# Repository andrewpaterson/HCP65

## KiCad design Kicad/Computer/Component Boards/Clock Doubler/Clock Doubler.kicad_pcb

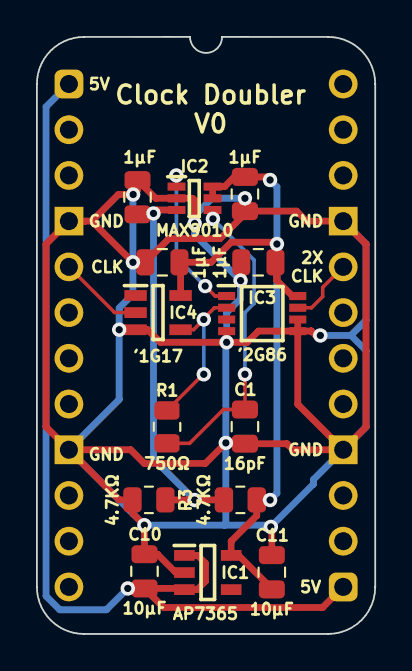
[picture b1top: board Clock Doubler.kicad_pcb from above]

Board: 2 copper layers, 18.8 x 33.2 mm, 15 parts (0 on the bottom side), 9 nets.

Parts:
C1: 16pF; C_0805
C2, C3, C4, C5: 1μF; C_0805
C10, C11: 10µF; C_0805
IC1: AP7365-33WG-7; SOT95P285X130-5N
IC2: MAX9010EXT+T; SOT65P210X110-6N
IC3: 74LVC2G86DP,125; SOP65P400X110-8N
IC4: 74LVC1G17GV,125; SOT95P275X110-5N
J1: Board 2x12 W15.24mm; DIP-24_Board_W15.24mm
R1: 750Ω; R_0805
R2, R3: 4.7KΩ; R_0805

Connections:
2x Fast CLK: IC3.7 (1Y), J1.20
5V: C10.1, IC1.1 (6VIn), IC1.3 (EN), J1.1, J1.13
/1.6V: C2.1, IC2.3 (IN+), R2.1, R3.2
/3.3V: C3.1, C4.1, C5.1, C11.1, IC1.5 (3.3VOut), IC2.5 (VCC), IC2.6 (VCC), IC3.8 (VCC), IC4.5 (3V), R2.2
/Clean Fast CLK: IC3.2 (1B), IC4.4 (Y), R1.2
Fast CLK: IC4.2 (A), J1.5
GND: C1.1, C2.2, C3.2, C4.2, C5.2, C10.2, C11.2, IC1.2 (GND), IC2.2 (GND), IC3.4 (GND), IC3.5 (2A), IC3.6 (2B), IC4.3 (GND), J1.4, J1.9, J1.16, J1.21, R3.1
unnamed: C1.2, IC2.4 (IN-), R1.1
unnamed: IC2.1 (OUT), IC3.1 (1A)

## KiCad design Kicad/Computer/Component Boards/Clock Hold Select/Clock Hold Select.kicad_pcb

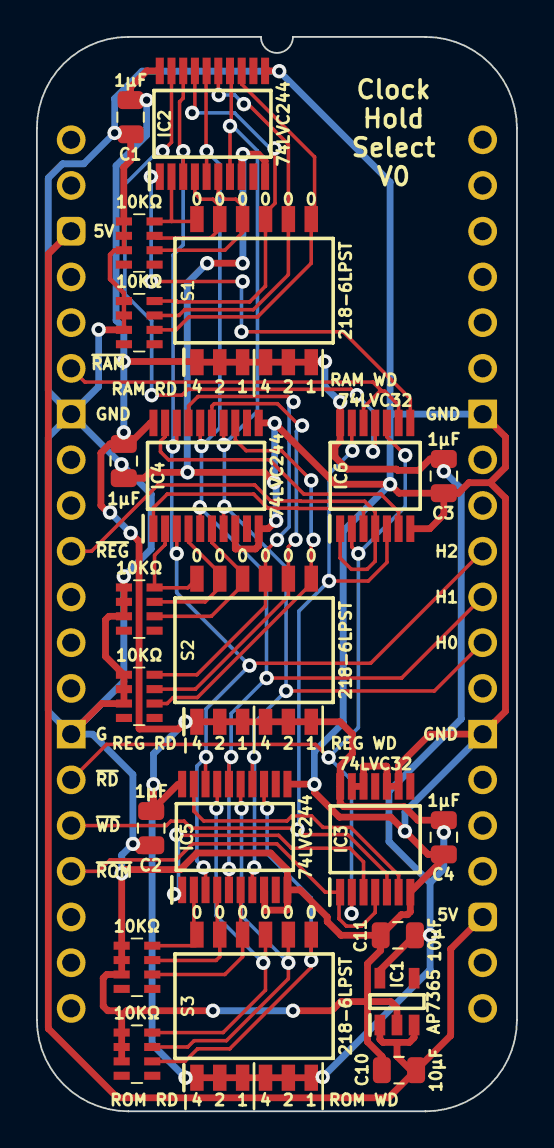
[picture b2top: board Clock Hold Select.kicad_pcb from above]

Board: 2 copper layers, 26.7 x 59.7 mm, 23 parts (0 on the bottom side), 35 nets.

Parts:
C1, C2, C3, C4, C12: 1μF; C_0805
C10, C11: 10µF; C_0805
IC1: AP7365-33WG-7; SOT95P285X130-5N
IC2, IC4, IC5: 74LVC244APW,118; SOP65P640X110-20N
IC3, IC6: 74LVC32APW,118; SOP65P640X110-14N
J1: Board 2x20 W22.86mm; DIP-40_Board_W22.86mm
RN1, RN2, RN3, RN4, RN5, RN6: CAY16-103J4LF; CAY16-J4
S1, S2, S3: 218-6LPST; SOIC127P844X265-12N

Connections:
5V: C10.1, IC1.1 (6VIn), IC1.3 (EN), J1.3, J1.23
/3.3V: C1.1, C2.1, C3.1, C4.1, C11.1, C12.1, IC1.5 (3.3VOut), IC2.20 (3V), IC3.14 (3V), IC4.20 (3V), IC5.20 (3V), IC6.14 (3V), S1.1, S1.2, S1.3, S1.4, S1.5, S1.6, S2.1, S2.2, S2.3, S2.4, S2.5, S2.6, S3.1, S3.2, S3.3, S3.4, S3.5, S3.6
/RAM RD H0: IC2.6 (1A2), RN1.6 (R3), S1.10
/RAM RD H1: IC2.4 (1A1), RN1.7 (R2), S1.11
/RAM RD H2: IC2.2 (1A0), RN1.8 (R1), S1.12
/RAM WD H0: IC2.13 (2A2), RN2.6 (R3), S1.7
/RAM WD H1: IC2.15 (2A1), RN2.7 (R2), S1.8
/RAM WD H2: IC2.17 (2A0), RN2.8 (R1), S1.9
/REG RD H0: IC4.6 (1A2), RN3.6 (R3), S2.10
/REG RD H1: IC4.4 (1A1), RN3.7 (R2), S2.11
/REG RD H2: IC4.2 (1A0), RN3.8 (R1), S2.12
/REG WD H0: IC4.13 (2A2), RN4.6 (R3), S2.7
/REG WD H1: IC4.15 (2A1), RN4.7 (R2), S2.8
/REG WD H2: IC4.17 (2A0), RN4.8 (R1), S2.9
/ROM RD H0: IC5.6 (1A2), RN5.6 (R3), S3.10
/ROM RD H1: IC5.4 (1A1), RN5.7 (R2), S3.11
/ROM RD H2: IC5.2 (1A0), RN5.8 (R1), S3.12
/ROM WD H0: IC5.13 (2A2), RN6.6 (R3), S3.7
/ROM WD H1: IC5.15 (2A1), RN6.7 (R2), S3.8
/ROM WD H2: IC5.17 (2A0), RN6.8 (R1), S3.9
/~RAM+~RD: IC2.1 (~1OE), IC6.8 (3Y)
/~RAM+~WD: IC2.19 (~2OE), IC6.11 (4Y)
/~REG+~RD: IC4.1 (~1OE), IC6.3 (1Y)
/~REG+~WD: IC4.19 (~2OE), IC6.6 (2Y)
/~ROM+~RD: IC3.3 (1Y), IC5.1 (~1OE)
/~ROM+~WD: IC3.6 (2Y), IC5.19 (~2OE)
GND: C1.2, C2.2, C3.2, C4.2, C10.2, C11.2, C12.2, IC1.2 (GND), IC2.8 (1A3), IC2.10 (GND), IC2.11 (2A3), IC3.7 (GND), IC3.9 (3A), IC3.10 (3B), IC3.12 (4A), IC3.13 (4B), IC4.8 (1A3), IC4.10 (GND), IC4.11 (2A3), IC5.8 (1A3), IC5.10 (GND), IC5.11 (2A3), IC6.7 (GND), J1.7, J1.14, J1.27, J1.34, RN1.1 (R1), RN1.2 (R2), RN1.3 (R3), RN2.1 (R1), RN2.2 (R2), RN2.3 (R3), RN3.1 (R1), RN3.2 (R2), RN3.3 (R3), RN4.1 (R1), RN4.2 (R2), RN4.3 (R3), RN5.1 (R1), RN5.2 (R2), RN5.3 (R3), RN6.1 (R1), RN6.2 (R2), RN6.3 (R3)
H0: IC2.7 (2Y2), IC2.14 (1Y2), IC4.7 (2Y2), IC4.14 (1Y2), IC5.7 (2Y2), IC5.14 (1Y2), J1.29
H1: IC2.5 (2Y1), IC2.16 (1Y1), IC4.5 (2Y1), IC4.16 (1Y1), IC5.5 (2Y1), IC5.16 (1Y1), J1.30
H2: IC2.3 (2Y0), IC2.18 (1Y0), IC4.3 (2Y0), IC4.18 (1Y0), IC5.3 (2Y0), IC5.18 (1Y0), J1.31
~Device RAM: IC6.9 (3A), IC6.12 (4A), J1.6
~Device ROM: IC3.1 (1A), IC3.4 (2A), J1.17
~Device Registers: IC6.1 (1A), IC6.4 (2A), J1.10
~RD: IC3.2 (1B), IC6.2 (1B), IC6.10 (3B), J1.15
~WD: IC3.5 (2B), IC6.5 (2B), IC6.13 (4B), J1.16

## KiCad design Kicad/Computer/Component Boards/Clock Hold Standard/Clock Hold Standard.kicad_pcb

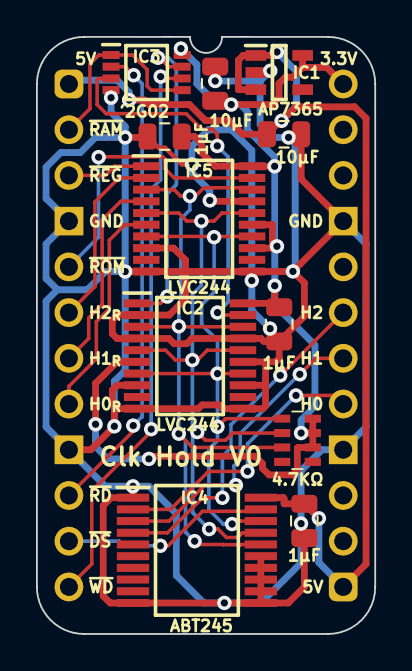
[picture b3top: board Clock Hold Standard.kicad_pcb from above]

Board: 2 copper layers, 18.8 x 33.2 mm, 12 parts (0 on the bottom side), 20 nets.

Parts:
C1, C2, C4: 1μF; C_0805
C10, C11: 10µF; C_0805
IC1: AP7365-33WG-7; SOT95P285X130-5N
IC2, IC5: 74LVC244APW,118; SOP65P640X110-20N
IC3: 74LVC2G02DP,125; SOP65P400X110-8N
IC4: SN74ABT245BDBR; SOP65P780X200-20N
J1: Board 2x12 W15.24mm; DIP-24_Board_W15.24mm
RN1: CAY16-472J4LF; CAY16-F4

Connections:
3.3V: C1.1, C2.1, C11.1, IC1.5 (3.3VOut), IC2.6 (1A2), IC2.20 (3V), IC3.8 (3V), IC5.13 (2A2), IC5.15 (2A1), IC5.20 (3V), J1.24, RN1.6 (R3), RN1.7 (R2), RN1.8 (R1)
5V: C4.1, C10.1, IC1.1 (6VIn), IC1.3 (EN), IC4.20 (5V), J1.1, J1.13
/H0: IC2.7 (2Y2), IC2.14 (1Y2), IC4.18 (B0), IC5.7 (2Y2), IC5.14 (1Y2), RN1.1 (R1)
/H1: IC2.5 (2Y1), IC2.16 (1Y1), IC4.17 (B1), IC5.5 (2Y1), IC5.16 (1Y1), RN1.2 (R2)
/H2: IC2.3 (2Y0), IC2.18 (1Y0), IC4.16 (B2), IC5.3 (2Y0), IC5.18 (1Y0), RN1.3 (R3)
/~RAM+~RD: IC2.1 (~1OE), IC3.7 (1Y)
/~RAM+~WD: IC2.19 (~2OE), IC3.3 (2Y)
GND: C1.2, C2.2, C4.2, C10.2, C11.2, IC1.2 (GND), IC2.2 (1A0), IC2.4 (1A1), IC2.8 (1A3), IC2.10 (GND), IC2.11 (2A3), IC2.13 (2A2), IC2.15 (2A1), IC2.17 (2A0), IC3.4 (GND), IC4.1 (DIR), IC4.10 (GND), IC4.11 (B7), IC4.12 (B6), IC4.13 (B5), IC4.14 (B4), IC4.15 (B3), IC5.8 (1A3), IC5.10 (GND), IC5.11 (2A3), IC5.17 (2A0), J1.4, J1.9, J1.16, J1.21
H0_{OUT}: IC4.2 (A0), J1.17
H0_{REG}: IC5.6 (1A2), J1.8
H1_{OUT}: IC4.3 (A1), J1.18
H1_{REG}: IC5.4 (1A1), J1.7
H2_{OUT}: IC4.4 (A2), J1.19
H2_{REG}: IC5.2 (1A0), J1.6
~Device RAM: IC3.1 (1A), IC3.5 (2A), J1.2
~Device ROM: IC5.19 (~2OE), J1.5
~Device Registers: IC5.1 (~1OE), J1.3
~Device Select: IC4.19 (~OE), J1.11
~RD: IC3.2 (1B), J1.10
~WD: IC3.6 (2B), J1.12

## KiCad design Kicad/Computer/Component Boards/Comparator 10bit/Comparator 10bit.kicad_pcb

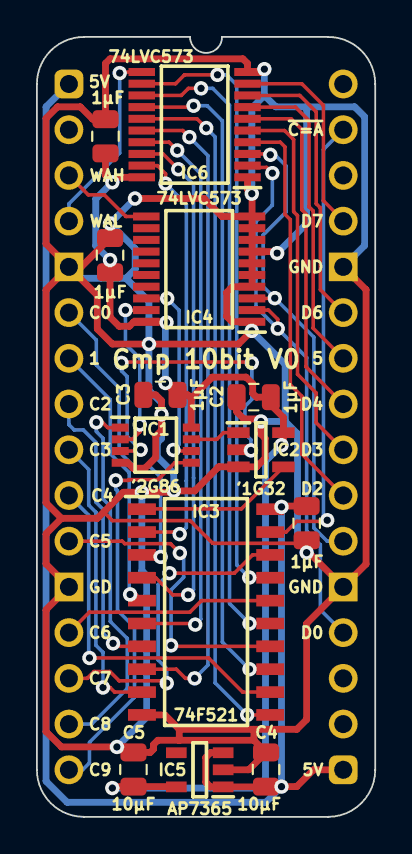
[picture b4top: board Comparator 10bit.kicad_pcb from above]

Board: 2 copper layers, 18.8 x 43.3 mm, 14 parts (0 on the bottom side), 37 nets.

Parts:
C1, C2, C3, C11, C12: 1μF; C_0805
C4, C5: 10µF; C_0805
IC1: 74LVC2G86DP,125; SOP65P400X110-8N
IC2: 74LVC1G32GV,125; SOT95P275X110-5N
IC3: SN74F521NSR; SOIC127P780X200-20N
IC4, IC6: 74LVC573APW,118; SOP65P640X110-20N
IC5: AP7365-33WG-7; SOT95P285X130-5N
J1: Board 2x16 W15.24mm; DIP-32_Board_W15.24mm

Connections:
5V: C4.1, C12.1, IC3.20 (5V), IC5.1 (6VIn), IC5.3 (EN), J1.1, J1.17
/3.3V: C1.1, C2.1, C3.1, C5.1, C11.1, IC1.8 (VCC), IC2.5 (3V), IC4.20 (3V), IC5.5 (3.3VOut), IC6.20 (3V)
/A0: IC3.2 (P0), IC6.19 (Q0)
/A1: IC3.4 (P1), IC6.18 (Q1)
/A2: IC3.6 (P2), IC6.17 (Q2)
/A3: IC3.8 (P3), IC6.16 (Q3)
/A4: IC3.11 (P4), IC6.15 (Q4)
/A5: IC3.13 (P5), IC6.14 (Q5)
/A6: IC3.15 (P6), IC6.13 (Q6)
/A7: IC3.17 (P7), IC6.12 (Q7)
/A8: IC1.2 (1B), IC4.19 (Q0)
/A8⊕C8: IC1.7 (1Y), IC2.1 (B)
/A9: IC1.6 (2B), IC4.18 (Q1)
/A9⊕C9: IC1.3 (2Y), IC2.2 (A)
/~C_{8..9=A_{8..9}}: IC2.4 (Y), IC3.1 (~OE)
C0: IC3.3 (Q0), J1.6
C1: IC3.5 (Q1), J1.7
C2: IC3.7 (Q2), J1.8
C3: IC3.9 (Q3), J1.9
C4: IC3.12 (Q4), J1.10
C5: IC3.14 (Q5), J1.11
C6: IC3.16 (Q6), J1.13
C7: IC3.18 (Q7), J1.14
C8: IC1.1 (1A), J1.15
C9: IC1.5 (2A), J1.16
D0: IC4.2 (D0), IC6.2 (D0), J1.20
D1: IC4.3 (D1), IC6.3 (D1), J1.22
D2: IC6.4 (D2), J1.23
D3: IC6.5 (D3), J1.24
D4: IC6.6 (D4), J1.25
D5: IC6.7 (D5), J1.26
D6: IC6.8 (D6), J1.27
D7: IC6.9 (D7), J1.29
GND: C1.2, C2.2, C3.2, C4.2, C5.2, C11.2, C12.2, IC1.4 (GND), IC2.3 (GND), IC3.10 (GND), IC4.1 (~OE), IC4.4 (D2), IC4.5 (D3), IC4.6 (D4), IC4.7 (D5), IC4.8 (D6), IC4.9 (D7), IC4.10 (GND), IC5.2 (GND), IC6.1 (~OE), IC6.10 (GND), J1.5, J1.12, J1.21, J1.28
Write A High: IC4.11 (LE), J1.3
Write A Low: IC6.11 (LE), J1.4
~C=A: IC3.19 (~P=Q), J1.31

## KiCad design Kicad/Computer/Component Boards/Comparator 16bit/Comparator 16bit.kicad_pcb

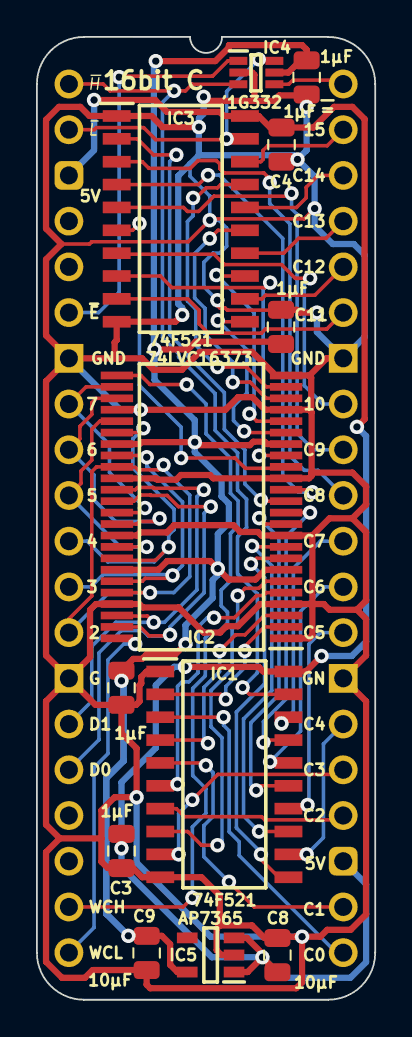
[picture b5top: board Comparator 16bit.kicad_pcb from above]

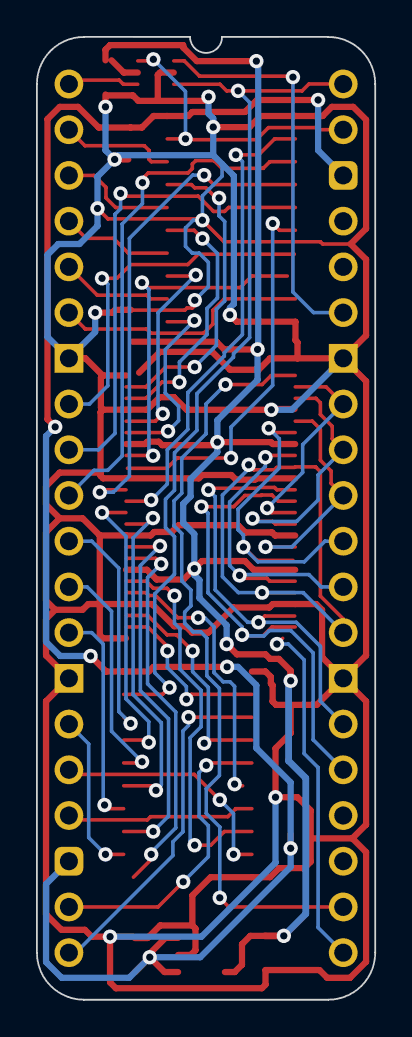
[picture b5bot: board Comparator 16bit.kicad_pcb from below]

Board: 2 copper layers, 18.8 x 53.5 mm, 15 parts (2 on the bottom side), 49 nets.

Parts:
C1, C2, C3, C4, C5: 1μF; C_0805
C8, C9: 10µF; C_0805
IC1, IC3: SN74F521NSR; SOIC127P780X200-20N
IC2: 74LVC16373ADL,118; SOP64P1025X280-48N
IC4: SN74LVC1G332DCKR; SOT65P210X110-6N
IC5: AP7365-33WG-7; SOT95P285X130-5N
J1, J3: Pin_Header_01x20; PinHeader_1x20_P2.54mm_Vertical
J2: Board 2x20 W15.24mm; DIP-40_Board_W15.24mm

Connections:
5V: C3.1, C4.1, C8.1, IC1.20 (5V), IC3.20 (5V), IC5.1 (6VIn), IC5.3 (EN), J2.3, J2.23
/3.3V: C1.1, C2.1, C5.1, C9.1, IC2.7 (3V), IC2.18 (3V), IC2.31 (3V), IC2.42 (3V), IC4.5 (3V), IC5.5 (3.3VOut)
/EC0: IC1.2 (P0), IC2.2 (1Q0)
/EC1: IC1.4 (P1), IC2.3 (1Q1)
/EC2: IC1.6 (P2), IC2.5 (1Q2)
/EC3: IC1.8 (P3), IC2.6 (1Q3)
/EC4: IC1.11 (P4), IC2.8 (1Q4)
/EC5: IC1.13 (P5), IC2.9 (1Q5)
/EC6: IC1.15 (P6), IC2.11 (1Q6)
/EC7: IC1.17 (P7), IC2.12 (1Q7)
/EC8: IC2.13 (2Q0), IC3.2 (P0)
/EC9: IC2.14 (2Q1), IC3.4 (P1)
/EC10: IC2.16 (2Q2), IC3.6 (P2)
/EC11: IC2.17 (2Q3), IC3.8 (P3)
/EC12: IC2.19 (2Q4), IC3.11 (P4)
/EC13: IC2.20 (2Q5), IC3.13 (P5)
/EC14: IC2.22 (2Q6), IC3.15 (P6)
/EC15: IC2.23 (2Q7), IC3.17 (P7)
C0: IC1.3 (Q0), J2.21
C1: IC1.5 (Q1), J2.22
C2: IC1.7 (Q2), J2.24
C3: IC1.9 (Q3), J2.25
C4: IC1.12 (Q4), J2.26
C5: IC1.14 (Q5), J2.28
C6: IC1.16 (Q6), J2.29
C7: IC1.18 (Q7), J2.30
C8: IC3.3 (Q0), J2.31
C9: IC3.5 (Q1), J2.32
C10: IC3.7 (Q2), J2.33
C11: IC3.9 (Q3), J2.35
C12: IC3.12 (Q4), J2.36
C13: IC3.14 (Q5), J2.37
C14: IC3.16 (Q6), J2.38
C15: IC3.18 (Q7), J2.39
D0: IC2.36 (2D0), IC2.47 (1D0), J2.16
D1: IC2.35 (2D1), IC2.46 (1D1), J2.15
D2: IC2.33 (2D2), IC2.44 (1D2), J2.13
D3: IC2.32 (2D3), IC2.43 (1D3), J2.12
D4: IC2.30 (2D4), IC2.41 (1D4), J2.11
D5: IC2.29 (2D5), IC2.40 (1D5), J2.10
D6: IC2.27 (2D6), IC2.38 (1D6), J2.9
D7: IC2.26 (2D7), IC2.37 (1D7), J2.8
GND: C1.2, C2.2, C3.2, C4.2, C5.2, C8.2, C9.2, IC1.1 (~OE), IC1.10 (GND), IC2.1 (1~OE), IC2.4 (GND), IC2.10 (GND), IC2.15 (GND), IC2.21 (GND), IC2.24 (2~OE), IC2.28 (GND), IC2.34 (GND), IC2.39 (GND), IC2.45 (GND), IC3.1 (~OE), IC3.10 (GND), IC4.2 (GND), IC5.2 (GND), J2.7, J2.14, J2.27, J2.34
Write Compare Address High: IC2.25 (2LE), J2.19
Write Compare Address Low: IC2.48 (1LE), J2.20
~OE: IC4.1 (A), J2.6
~P=Q: IC4.4 (Y), J2.40
~PH=QH: IC1.19 (~P=Q), IC4.3 (B), J2.1
~PL=QL: IC3.19 (~P=Q), IC4.6 (C), J2.2

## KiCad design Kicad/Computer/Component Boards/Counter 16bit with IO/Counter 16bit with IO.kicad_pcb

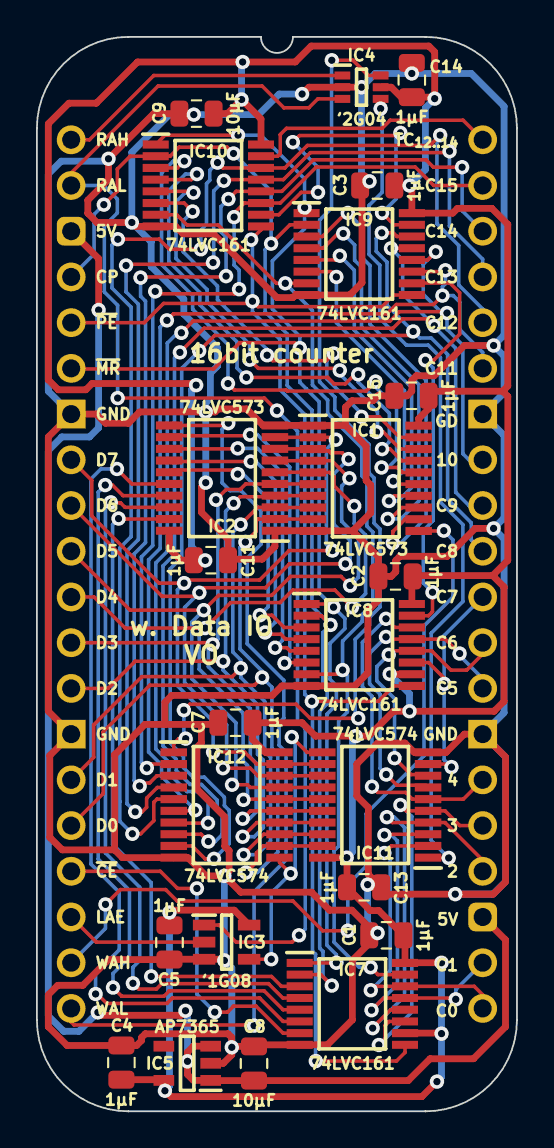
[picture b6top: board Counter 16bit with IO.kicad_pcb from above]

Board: 2 copper layers, 26.7 x 59.7 mm, 24 parts (0 on the bottom side), 59 nets.

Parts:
C1, C2, C3, C4, C5, C7, C11, C13, C14, C15: 1μF; C_0805
C8, C9: 10µF; C_0805
IC1, IC2: 74LVC573APW,118; SOP65P640X110-20N
IC3: 74LVC1G08GV,125; SOT95P275X110-5N
IC4: 74LVC2G04GW-Q100H; SOP65P210X110-6N
IC5: AP7365-33WG-7; SOT95P285X130-5N
IC7, IC8, IC9, IC10: 74LVC161PW,112; SOP65P640X110-16N
IC11, IC12: 74LVC574APW,118; SOP65P640X110-20N
J2: Board 2x20 W22.86mm; DIP-40_Board_W22.86mm

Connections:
5V: C8.1, IC5.1 (6VIn), IC5.3 (EN), J2.3, J2.23
/3.3V: C1.1, C2.1, C3.1, C4.1, C5.1, C7.1, C9.1, C11.1, C13.1, C14.1, C15.1, IC1.20 (3V), IC2.20 (3V), IC3.5 (3V), IC4.5 (3V), IC5.5 (3.3VOut), IC7.10 (CET), IC7.16 (3V), IC8.10 (CET), IC8.16 (3V), IC9.16 (3V), IC10.16 (3V), IC11.20 (3V), IC12.20 (3V)
/LC0: IC2.19 (Q0), IC7.3 (D0)
/LC1: IC2.18 (Q1), IC7.4 (D1)
/LC2: IC2.17 (Q2), IC7.5 (D2)
/LC3: IC2.16 (Q3), IC7.6 (D3)
/LC4: IC2.15 (Q4), IC8.3 (D0)
/LC5: IC2.14 (Q5), IC8.4 (D1)
/LC6: IC2.13 (Q6), IC8.5 (D2)
/LC7: IC2.12 (Q7), IC8.6 (D3)
/LC8: IC1.12 (Q7), IC9.3 (D0)
/LC9: IC1.13 (Q6), IC9.4 (D1)
/LC10: IC1.14 (Q5), IC9.5 (D2)
/LC11: IC1.15 (Q4), IC9.6 (D3)
/LC12: IC1.16 (Q3), IC10.3 (D0)
/LC13: IC1.17 (Q2), IC10.4 (D1)
/LC14: IC1.18 (Q1), IC10.5 (D2)
/LC15: IC1.19 (Q0), IC10.6 (D3)
/Latch Address: IC3.4 (Y), IC11.11 (CP), IC12.11 (CP)
/TC_{0..3}: IC7.15 (TC), IC8.7 (CEP), IC9.7 (CEP), IC10.7 (CEP)
/TC_{4..7}: IC8.15 (TC), IC9.10 (CET)
/TC_{8..11}: IC9.15 (TC), IC10.10 (CET)
/~Read Address High: IC4.6 (1Y), IC12.1 (~OE)
/~Read Address Low: IC4.4 (2Y), IC11.1 (~OE)
C0: IC7.14 (Q0), IC11.2 (D0), J2.21
C1: IC7.13 (Q1), IC11.3 (D1), J2.22
C2: IC7.12 (Q2), IC11.4 (D2), J2.24
C3: IC7.11 (Q3), IC11.5 (D3), J2.25
C4: IC8.14 (Q0), IC11.6 (D4), J2.26
C5: IC8.13 (Q1), IC11.7 (D5), J2.28
C6: IC8.12 (Q2), IC11.8 (D6), J2.29
C7: IC8.11 (Q3), IC11.9 (D7), J2.30
C8: IC9.14 (Q0), IC12.9 (D7), J2.31
C9: IC9.13 (Q1), IC12.8 (D6), J2.32
C10: IC9.12 (Q2), IC12.7 (D5), J2.33
C11: IC9.11 (Q3), IC12.6 (D4), J2.35
C12: IC10.14 (Q0), IC12.5 (D3), J2.36
C13: IC10.13 (Q1), IC12.4 (D2), J2.37
C14: IC10.12 (Q2), IC12.3 (D1), J2.38
C15: IC10.11 (Q3), IC12.2 (D0), J2.39
CLK: IC7.2 (CP), IC8.2 (CP), IC9.2 (CP), IC10.2 (CP), J2.4
Count Enable: IC7.7 (CEP), J2.17
D0: IC1.9 (D7), IC2.2 (D0), IC11.19 (Q0), IC12.12 (Q7), J2.16
D1: IC1.8 (D6), IC2.3 (D1), IC11.18 (Q1), IC12.13 (Q6), J2.15
D2: IC1.7 (D5), IC2.4 (D2), IC11.17 (Q2), IC12.14 (Q5), J2.13
D3: IC1.6 (D4), IC2.5 (D3), IC11.16 (Q3), IC12.15 (Q4), J2.12
D4: IC1.5 (D3), IC2.6 (D4), IC11.15 (Q4), IC12.16 (Q3), J2.11
D5: IC1.4 (D2), IC2.7 (D5), IC11.14 (Q5), IC12.17 (Q2), J2.10
D6: IC1.3 (D1), IC2.8 (D6), IC11.13 (Q6), IC12.18 (Q1), J2.9
D7: IC1.2 (D0), IC2.9 (D7), IC11.12 (Q7), IC12.19 (Q0), J2.8
GND: C1.2, C2.2, C3.2, C4.2, C5.2, C7.2, C8.2, C9.2, C11.2, C13.2, C14.2, C15.2, IC1.1 (~OE), IC1.10 (GND), IC2.1 (~OE), IC2.10 (GND), IC3.3 (GND), IC4.2 (GND), IC5.2 (GND), IC7.8 (GND), IC8.8 (GND), IC9.8 (GND), IC10.8 (GND), IC11.10 (GND), IC12.10 (GND), J2.7, J2.14, J2.27, J2.34
Latch Address Enable: IC3.2 (A), J2.18
Read Address High: IC4.1 (1A), J2.1
Read Address Low: IC3.1 (B), IC4.3 (2A), J2.2
TC_{12..15}: IC10.15 (TC), J2.40
Write Start Address High: IC1.11 (LE), J2.19
Write Start Address Low: IC2.11 (LE), J2.20
~Load Count Start: IC7.9 (~PE), IC8.9 (~PE), IC9.9 (~PE), IC10.9 (~PE), J2.5
~Reset: IC7.1 (~MR), IC8.1 (~MR), IC9.1 (~MR), IC10.1 (~MR), J2.6

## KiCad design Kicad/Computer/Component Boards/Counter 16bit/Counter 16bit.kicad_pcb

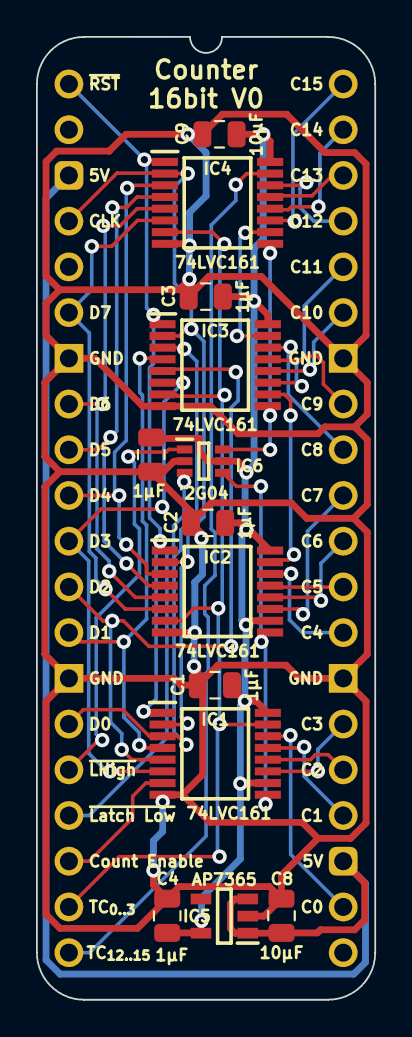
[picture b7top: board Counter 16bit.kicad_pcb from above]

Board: 2 copper layers, 18.8 x 53.5 mm, 14 parts (0 on the bottom side), 38 nets.

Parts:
C1, C2, C3, C4, C5: 1μF; C_0805
C8, C9: 10µF; C_0805
IC1, IC2, IC3, IC4: 74LVC161PW,112; SOP65P640X110-16N
IC5: AP7365-33WG-7; SOT95P285X130-5N
IC6: 74LVC2G04GW-Q100H; SOP65P210X110-6N
J1: Board 2x20 W15.24mm; DIP-40_Board_W15.24mm

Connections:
5V: C8.1, IC5.1 (6VIn), IC5.3 (EN), J1.3, J1.23
/3.3V: C1.1, C2.1, C3.1, C4.1, C5.1, C9.1, IC1.10 (CET), IC1.16 (3V), IC2.10 (CET), IC2.16 (3V), IC3.16 (3V), IC4.16 (3V), IC5.5 (3.3VOut), IC6.5 (3V)
/TC_{4..7}: IC2.15 (TC), IC3.10 (CET)
/TC_{8..11}: IC3.15 (TC), IC4.10 (CET)
/~Latch High: IC3.9 (~PE), IC4.9 (~PE), IC6.6 (1Y)
/~Latch Low: IC1.9 (~PE), IC2.9 (~PE), IC6.4 (2Y)
C0: IC1.14 (Q0), J1.22
C1: IC1.13 (Q1), J1.24
C2: IC1.12 (Q2), J1.25
C3: IC1.11 (Q3), J1.26
C4: IC2.14 (Q0), J1.28
C5: IC2.13 (Q1), J1.29
C6: IC2.12 (Q2), J1.30
C7: IC2.11 (Q3), J1.31
C8: IC3.14 (Q0), J1.32
C9: IC3.13 (Q1), J1.33
C10: IC3.12 (Q2), J1.35
C11: IC3.11 (Q3), J1.36
C12: IC4.14 (Q0), J1.37
C13: IC4.13 (Q1), J1.38
C14: IC4.12 (Q2), J1.39
C15: IC4.11 (Q3), J1.40
CLK: IC1.2 (CP), IC2.2 (CP), IC3.2 (CP), IC4.2 (CP), J1.4
Count Enable: IC1.7 (CEP), J1.18
D0: IC1.3 (D0), IC3.3 (D0), J1.15
D1: IC1.4 (D1), IC3.4 (D1), J1.13
D2: IC1.5 (D2), IC3.5 (D2), J1.12
D3: IC1.6 (D3), IC3.6 (D3), J1.11
D4: IC2.3 (D0), IC4.3 (D0), J1.10
D5: IC2.4 (D1), IC4.4 (D1), J1.9
D6: IC2.5 (D2), IC4.5 (D2), J1.8
D7: IC2.6 (D3), IC4.6 (D3), J1.6
GND: C1.2, C2.2, C3.2, C4.2, C5.2, C8.2, C9.2, IC1.8 (GND), IC2.8 (GND), IC3.8 (GND), IC4.8 (GND), IC5.2 (GND), IC6.2 (GND), J1.7, J1.14, J1.27, J1.34
Latch High: IC6.1 (1A), J1.16
Latch Low: IC6.3 (2A), J1.17
TC_{0..3}: IC1.15 (TC), IC2.7 (CEP), IC3.7 (CEP), IC4.7 (CEP), J1.19
TC_{12..15}: IC4.15 (TC), J1.20
~Reset: IC1.1 (~MR), IC2.1 (~MR), IC3.1 (~MR), IC4.1 (~MR), J1.1

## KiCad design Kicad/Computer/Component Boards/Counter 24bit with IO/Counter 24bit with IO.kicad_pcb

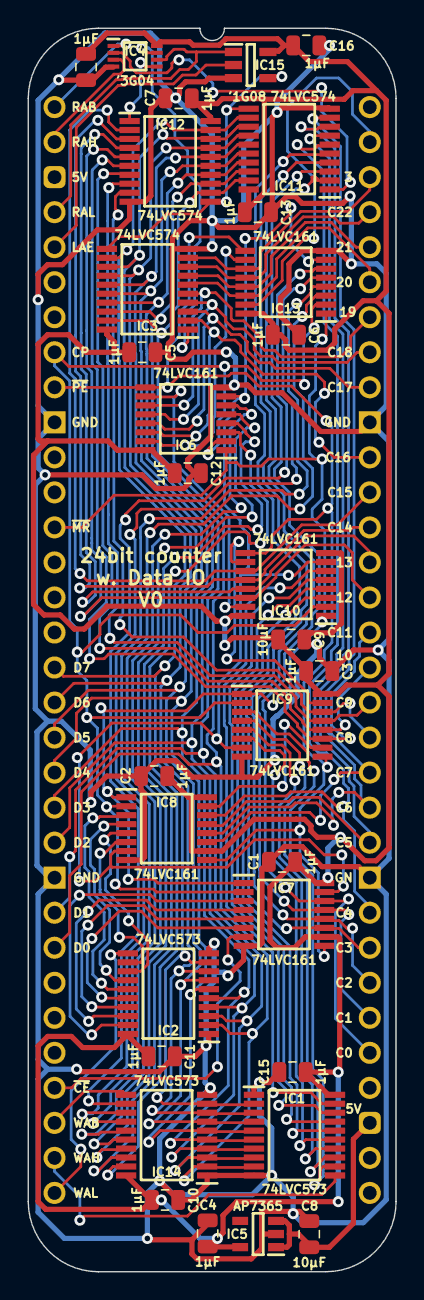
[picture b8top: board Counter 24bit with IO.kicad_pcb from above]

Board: 2 copper layers, 26.7 x 90.2 mm, 32 parts (0 on the bottom side), 80 nets.

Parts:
C1, C2, C3, C4, C5, C6, C7, C10, C11, C12, C13, C14, C15, C16: 1μF; C_0805
C8, C9: 10µF; C_0805
IC1, IC2, IC14: 74LVC573APW,118; SOP65P640X110-20N
IC3, IC11, IC12: 74LVC574APW,118; SOP65P640X110-20N
IC4: SN74LVC3G04DCUR; SOP50P310X90-8N
IC5: AP7365-33WG-7; SOT95P285X130-5N
IC6, IC7, IC8, IC9, IC10, IC13: 74LVC161PW,112; SOP65P640X110-16N
IC15: 74LVC1G08GV,125; SOT95P275X110-5N
J1: Board 2x32 W22.86mm; DIP-64_Board_W22.86mm

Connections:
5V: C8.1, IC5.1 (6VIn), IC5.3 (EN), J1.35
/3.3V: C1.1, C2.1, C3.1, C4.1, C5.1, C6.1, C7.1, C9.1, C10.1, C11.1, C12.1, C13.1, C14.1, C15.1, C16.1, IC1.20 (3V), IC2.20 (3V), IC3.20 (3V), IC4.8 (3V), IC5.5 (3.3VOut), IC6.16 (3V), IC7.10 (CET), IC7.16 (3V), IC8.10 (CET), IC8.16 (3V), IC9.16 (3V), IC10.16 (3V), IC11.20 (3V), IC12.20 (3V), IC13.16 (3V), IC14.20 (3V), IC15.5 (3V)
/LC0: IC2.19 (Q0), IC7.3 (D0)
/LC1: IC2.18 (Q1), IC7.4 (D1)
/LC2: IC2.17 (Q2), IC7.5 (D2)
/LC3: IC2.16 (Q3), IC7.6 (D3)
/LC4: IC2.15 (Q4), IC8.3 (D0)
/LC5: IC2.14 (Q5), IC8.4 (D1)
/LC6: IC2.13 (Q6), IC8.5 (D2)
/LC7: IC2.12 (Q7), IC8.6 (D3)
/LC8: IC1.12 (Q7), IC9.3 (D0)
/LC9: IC1.13 (Q6), IC9.4 (D1)
/LC10: IC1.14 (Q5), IC9.5 (D2)
/LC11: IC1.15 (Q4), IC9.6 (D3)
/LC12: IC1.16 (Q3), IC10.3 (D0)
/LC13: IC1.17 (Q2), IC10.4 (D1)
/LC14: IC1.18 (Q1), IC10.5 (D2)
/LC15: IC1.19 (Q0), IC10.6 (D3)
/LC16: IC6.3 (D0), IC14.19 (Q0)
/LC17: IC6.4 (D1), IC14.18 (Q1)
/LC18: IC6.5 (D2), IC14.17 (Q2)
/LC19: IC6.6 (D3), IC14.16 (Q3)
/LC20: IC13.3 (D0), IC14.15 (Q4)
/LC21: IC13.4 (D1), IC14.14 (Q5)
/LC22: IC13.5 (D2), IC14.13 (Q6)
/LC23: IC13.6 (D3), IC14.12 (Q7)
/Latch Read Count: IC3.11 (CP), IC11.11 (CP), IC12.11 (CP), IC15.4 (Y)
/TC_{0..3}: IC6.7 (CEP), IC7.15 (TC), IC8.7 (CEP), IC9.7 (CEP), IC10.7 (CEP), IC13.7 (CEP)
/TC_{4..7}: IC8.15 (TC), IC9.10 (CET)
/TC_{8..11}: IC9.15 (TC), IC10.10 (CET)
/TC_{12..15}: IC6.10 (CET), IC10.15 (TC)
/TC_{16..19}: IC6.15 (TC), IC13.10 (CET)
/~Read Count Bank: IC3.1 (~OE), IC4.7 (1Y)
/~Read Count High: IC4.5 (2Y), IC12.1 (~OE)
/~Read Count Low: IC4.2 (3Y), IC11.1 (~OE)
C0: IC7.14 (Q0), IC11.2 (D0), J1.37
C1: IC7.13 (Q1), IC11.3 (D1), J1.38
C2: IC7.12 (Q2), IC11.4 (D2), J1.39
C3: IC7.11 (Q3), IC11.5 (D3), J1.40
C4: IC8.14 (Q0), IC11.6 (D4), J1.41
C5: IC8.13 (Q1), IC11.7 (D5), J1.43
C6: IC8.12 (Q2), IC11.8 (D6), J1.44
C7: IC8.11 (Q3), IC11.9 (D7), J1.45
C8: IC9.14 (Q0), IC12.9 (D7), J1.46
C9: IC9.13 (Q1), IC12.8 (D6), J1.47
C10: IC9.12 (Q2), IC12.7 (D5), J1.48
C11: IC9.11 (Q3), IC12.6 (D4), J1.49
C12: IC10.14 (Q0), IC12.5 (D3), J1.50
C13: IC10.13 (Q1), IC12.4 (D2), J1.51
C14: IC10.12 (Q2), IC12.3 (D1), J1.52
C15: IC10.11 (Q3), IC12.2 (D0), J1.53
C16: IC3.2 (D0), IC6.14 (Q0), J1.54
C17: IC3.3 (D1), IC6.13 (Q1), J1.56
C18: IC3.4 (D2), IC6.12 (Q2), J1.57
C19: IC3.5 (D3), IC6.11 (Q3), J1.58
C20: IC3.6 (D4), IC13.14 (Q0), J1.59
C21: IC3.7 (D5), IC13.13 (Q1), J1.60
C22: IC3.8 (D6), IC13.12 (Q2), J1.61
C23: IC3.9 (D7), IC13.11 (Q3), J1.62
CLK: IC6.2 (CP), IC7.2 (CP), IC8.2 (CP), IC9.2 (CP), IC10.2 (CP), IC13.2 (CP), J1.8
Count Enable: IC7.7 (CEP), J1.29
D0: IC1.9 (D7), IC2.2 (D0), IC3.19 (Q0), IC11.19 (Q0), IC12.12 (Q7), IC14.2 (D0), J1.25
D1: IC1.8 (D6), IC2.3 (D1), IC3.18 (Q1), IC11.18 (Q1), IC12.13 (Q6), IC14.3 (D1), J1.24
D2: IC1.7 (D5), IC2.4 (D2), IC3.17 (Q2), IC11.17 (Q2), IC12.14 (Q5), IC14.4 (D2), J1.22
D3: IC1.6 (D4), IC2.5 (D3), IC3.16 (Q3), IC11.16 (Q3), IC12.15 (Q4), IC14.5 (D3), J1.21
D4: IC1.5 (D3), IC2.6 (D4), IC3.15 (Q4), IC11.15 (Q4), IC12.16 (Q3), IC14.6 (D4), J1.20
D5: IC1.4 (D2), IC2.7 (D5), IC3.14 (Q5), IC11.14 (Q5), IC12.17 (Q2), IC14.7 (D5), J1.19
D6: IC1.3 (D1), IC2.8 (D6), IC3.13 (Q6), IC11.13 (Q6), IC12.18 (Q1), IC14.8 (D6), J1.18
D7: IC1.2 (D0), IC2.9 (D7), IC3.12 (Q7), IC11.12 (Q7), IC12.19 (Q0), IC14.9 (D7), J1.17
Enable Latch Read Count: IC15.2 (A), J1.5
GND: C1.2, C2.2, C3.2, C4.2, C5.2, C6.2, C7.2, C8.2, C9.2, C10.2, C11.2, C12.2, C13.2, C14.2, C15.2, C16.2, IC1.1 (~OE), IC1.10 (GND), IC2.1 (~OE), IC2.10 (GND), IC3.10 (GND), IC4.4 (GND), IC5.2 (GND), IC6.8 (GND), IC7.8 (GND), IC8.8 (GND), IC9.8 (GND), IC10.8 (GND), IC11.10 (GND), IC12.10 (GND), IC13.8 (GND), IC14.1 (~OE), IC14.10 (GND), IC15.3 (GND), J1.10, J1.23, J1.42, J1.55
Read Count Bank: IC4.1 (1A), J1.1
Read Count High: IC4.3 (2A), J1.2
Read Count Low: IC4.6 (3A), IC15.1 (B), J1.4
TC_{20..23}: IC13.15 (TC), J1.63
Write Start Bank: IC14.11 (LE), J1.30
Write Start High: IC1.11 (LE), J1.31
Write Start Low: IC2.11 (LE), J1.32
~Load Count Start: IC6.9 (~PE), IC7.9 (~PE), IC8.9 (~PE), IC9.9 (~PE), IC10.9 (~PE), IC13.9 (~PE), J1.9
~Reset: IC6.1 (~MR), IC7.1 (~MR), IC8.1 (~MR), IC9.1 (~MR), IC10.1 (~MR), IC13.1 (~MR), J1.13
